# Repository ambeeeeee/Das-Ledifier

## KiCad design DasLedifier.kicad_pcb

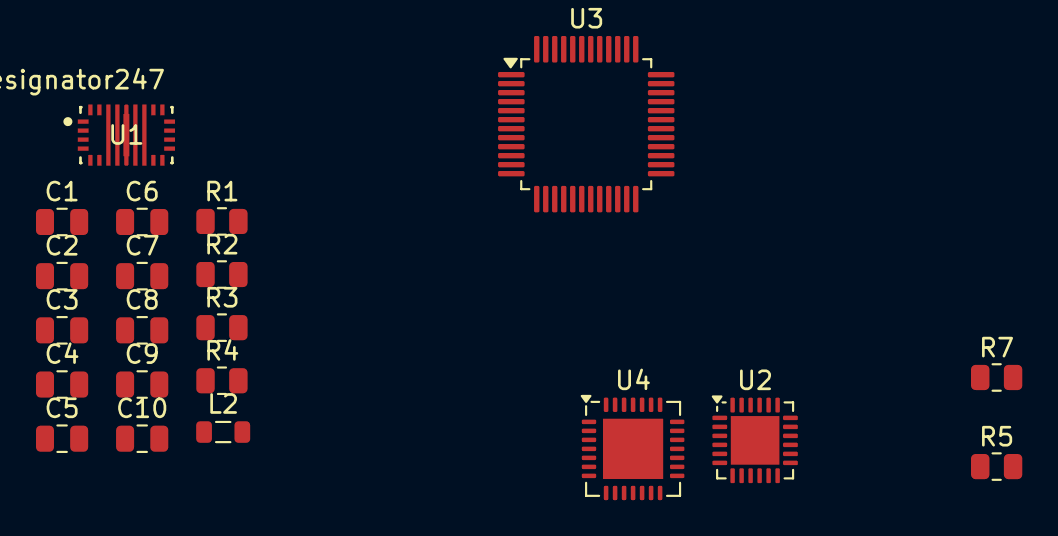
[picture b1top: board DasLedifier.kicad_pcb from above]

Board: 2 copper layers, 21 parts (0 on the bottom side), 17 nets, no tracks yet.

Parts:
C1, C5, C7, C9: 22uF; C_0805_2012Metric
C2, C3, C4, C6, C8, C10: C_Small; C_0805_2012Metric
L2: 4.7uH; L_0805_2012Metric
R1: R; R_0805_2012Metric
R2, R4, R5, R7: R_Small; R_0805_2012Metric
R3: 0k; R_0805_2012Metric
U1: PTPS55289RYQR; RYQ0021A-MFG
U2: STUSB4500QTR; QFN-24-1EP_4x4mm_P0.5mm_EP2.7x2.7mm
U3: STM32F070CBTx; LQFP-48_7x7mm_P0.5mm
U4: CC2520; QFN-28-1EP_5x5mm_P0.5mm_EP3.35x3.35mm

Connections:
/LED_SUPPLY/AGND: C6.2, C8.2, C10.2, R3.1, R4.2, R5.2, U1.17 (AGND)
/LED_SUPPLY/BOOT1: C3.1, U1.20 (BOOT1)
/LED_SUPPLY/BOOT2: C4.2, U1.19 (BOOT2)
/LED_SUPPLY/CDC: R5.1, U1.16 (CDC)
/LED_SUPPLY/COMP: C2.1, R2.1, U1.15 (COMP)
/LED_SUPPLY/FSW: C10.1, U1.6 (FSW)
/LED_SUPPLY/ISP: C1.1, C5.1, C7.1, C9.1, R1.1, U1.11 (VOUT), U1.12 (ISP)
/LED_SUPPLY/SW1: C3.2, L2.1, U1.8 (SW1)
/LED_SUPPLY/SW2: C4.1, L2.2, U1.10 (SW2)
/LED_SUPPLY/SYNC: R4.1, U1.5 (DITH_SYNC)
GND: C1.2, C5.2, C7.2, C9.2, R3.2, U1.9 (PGND)
unnamed: C2.2, C6.1, R2.2
unnamed: R7.2, U1.1 (EN_UVLO), U1.2 (MODE)
unnamed: U2.10 (GND), U2.25 (GND)
unnamed: U3.23 (VSS), U3.35 (VSS), U3.47 (VSS)
VCC: C8.1, U1.18 (VCC)
VDD: R1.2, R7.1, U1.13 (ISN)

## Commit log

2024-02-21 Initial Schematic Commit
2024-02-26 More Schematic Work
2024-02-27 Last commit of v1
2024-03-11 Progress
2024-03-12 Basic STM32 hook-up and reference
2024-03-12 Switch to new chip
2024-03-13 Haven't checked LSE, NRST, BOOT0 and SWD
